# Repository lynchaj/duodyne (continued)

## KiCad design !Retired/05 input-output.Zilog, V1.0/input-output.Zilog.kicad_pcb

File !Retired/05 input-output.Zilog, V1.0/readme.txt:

The input-output.Zilog board provides system timer/counter, dual serial ports, and dual general purpose parallel IO.  It also supports a dedicated controller for extended interrupts.  Designed for IM2, it is intended to be the primary console interface.

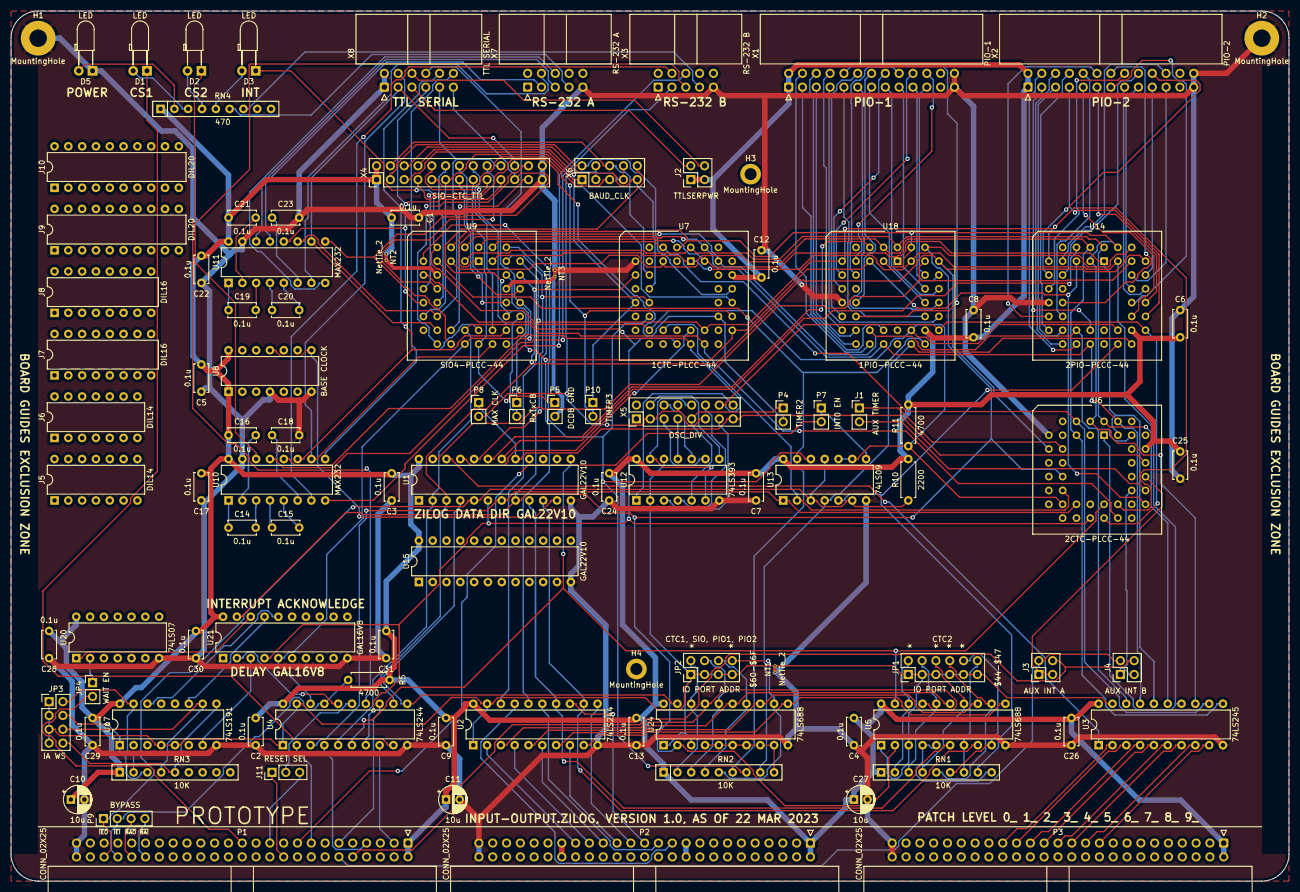
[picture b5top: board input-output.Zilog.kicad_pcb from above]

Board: 2 copper layers, 235.0 x 160.0 mm, 102 parts (0 on the bottom side), 210 nets.

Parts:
C1, C2, C3, C4, C5, C6, C7, C8, C9, C12, C13, C14, C15, C16, C17, C18, C19, C20, C21, C22, C23, C24, C25, C26, C28, C29, C30, C31: 0.1u; C_Disc_D5.0mm_W2.5mm_P5.00mm
C10, C11, C27: 10u; CP_Radial_D5.0mm_P2.50mm
D1, D2, D3, D5: LED; LED_D3.0mm_Horizontal_O3.81mm_Z2.0mm
H1, H2: MountingHole; MountingHole_3.2mm_M3_Pad
H3, H4: MountingHole; MountingHole_2.2mm_M2_DIN965_Pad
J1: AUX TIMER; PinHeader_1x02_P2.54mm_Vertical
J2: TTLSERPWR; PinHeader_2x02_P2.54mm_Vertical
J3: AUX INT A; PinHeader_2x02_P2.54mm_Vertical
J4: AUX INT B; PinHeader_2x02_P2.54mm_Vertical
J5, J6: DIL14; DIP-14_W7.62mm
J7, J8: DIL16; DIP-16_W7.62mm
J9, J10: DIL20; DIP-20_W7.62mm
J11: RESET SEL; PinHeader_1x03_P2.54mm_Vertical
JP1: IO PORT ADDR; PinHeader_2x06_P2.54mm_Vertical
JP2: IO PORT ADDR; PinHeader_2x04_P2.54mm_Vertical
JP3: IA WS; PinHeader_2x04_P2.54mm_Vertical
JP4: WAIT EN; PinHeader_1x02_P2.54mm_Vertical
NT1, NT2, NT3: NetTie_2; NetTie-2_THT_Pad0.3mm
P1, P2, P3: CONN_02X25; IDC-Header_2x25_P2.54mm_Horizontal
P4: TIMER2; PinHeader_1x02_P2.54mm_Vertical
P5: DCDB GND; PinHeader_1x02_P2.54mm_Vertical
P6: RxTxCB; PinHeader_1x02_P2.54mm_Vertical
P7: INT0 EN; PinHeader_1x02_P2.54mm_Vertical
P8: MAX CLK; PinHeader_1x02_P2.54mm_Vertical
P9: BYPASS; PinHeader_1x04_P2.54mm_Vertical
P10: TIMER3; PinHeader_1x02_P2.54mm_Vertical
R5, R11: 4700; R_Axial_DIN0207_L6.3mm_D2.5mm_P7.62mm_Horizontal
R10: 2200; R_Axial_DIN0207_L6.3mm_D2.5mm_P7.62mm_Horizontal
RN1, RN2, RN3: 10K; R_Array_SIP9
RN4: 470; R_Array_SIP9
U1, U15: GAL22V10; DIP-24_W7.62mm
U2, U4: 74LS244; DIP-20_W7.62mm
U3: 74LS245; DIP-20_W7.62mm
U5, U24: 74LS688; DIP-20_W7.62mm
U6: 2CTC-PLCC-44; PLCC-44_THT-Socket
U7: 1CTC-PLCC-44; PLCC-44_THT-Socket
U8: BASE CLOCK; DIP-14_W7.62mm
U9: SIO4-PLCC-44; PLCC-44_THT-Socket
U10, U11: MAX232; DIP-16_W7.62mm
U12: 74LS393; DIP-14_W7.62mm
U13: 74LS09; DIP-14_W7.62mm
U14: 2PIO-PLCC-44; PLCC-44_THT-Socket
U17: 74LS191; DIP-16_W7.62mm
U18: 1PIO-PLCC-44; PLCC-44_THT-Socket
U20: 74LS07; DIP-14_W7.62mm
U21: GAL16V8; DIP-20_W7.62mm
X1: PIO-1; IDC-Header_2x13_P2.54mm_Horizontal
X2: PIO-2; IDC-Header_2x13_P2.54mm_Horizontal
X3: RS-232 B; IDC-Header_2x05_P2.54mm_Horizontal
X4: SIO-CTC_TTL; PinHeader_2x13_P2.54mm_Vertical
X5: OSC_DIV; PinHeader_2x08_P2.54mm_Vertical
X6: BAUD_CLK; PinHeader_2x05_P2.54mm_Vertical
X7: RS-232 A; IDC-Header_2x05_P2.54mm_Horizontal
X8: TTL SERIAL; IDC-Header_2x06_P2.54mm_Horizontal

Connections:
470A: D5.2 (A), RN4.2 (R1)
470B: D1.2 (A), RN4.3 (R2)
470C: D2.2 (A), RN4.4 (R3)
470D: D3.2 (A), RN4.5 (R4)
470E: RN4.6 (R5), X7.7
470F: RN4.7 (R6), X3.7
+12V: P2.19, P2.20
-12V: P2.37, P2.38
/CTC-INT/2CTC_TG1: J3.1, J3.3, U6.33 (CLK/TRG1)
/CTC-INT/2CTC_TG2: J4.1, J4.3, U6.32 (CLK/TRG2)
/CTC-INT/2CTC_TG3: J1.2, U6.31 (CLK/TRG3)
/CTC-INT/2CTC_ZC0: J1.1, U6.10 (ZC/TO0)
/CTC-SIO/1CPA: U12.1 (CP), X5.16
/CTC-SIO/1CTC_TG0: U7.35 (CLK/TRG0), X4.3, X6.2
/CTC-SIO/1CTC_TG1: U7.33 (CLK/TRG1), X4.5, X6.1
/CTC-SIO/1CTC_TG2: P4.2, U7.32 (CLK/TRG2), X4.7
/CTC-SIO/1CTC_TG3: P10.2, U7.31 (CLK/TRG3), X4.9
/CTC-SIO/1CTC_ZC0: U7.10 (ZC/TO0), X4.4, X6.6
/CTC-SIO/1CTC_ZC1: U7.12 (ZC/TO1), X4.6, X6.9
/CTC-SIO/1CTC_ZC2: P10.1, U7.13 (ZC/TO2), X4.8
/CTC-SIO/1CTSA_IN: U11.8 (R2IN), X7.6
/CTC-SIO/1CTSB_IN: U10.8 (R2IN), X3.6
/CTC-SIO/1PHI_X: P8.2 (B), X5.3, X5.8, X5.11, X6.3, X6.4, X6.7, X6.8
/CTC-SIO/1PWRA: J2.2, X8.5
/CTC-SIO/1PWRB: J2.4, X8.6
/CTC-SIO/1Q0A: U12.3 (Q0), X5.13
/CTC-SIO/1Q0B: U12.11 (Q0), X5.7
/CTC-SIO/1Q1A: U12.4 (Q1), X5.12
/CTC-SIO/1Q1B: U12.10 (Q1), X5.6
/CTC-SIO/1Q2A: P4.1, U12.5 (Q2), X5.9
/CTC-SIO/1Q2B: U12.9 (Q2), X5.5
/CTC-SIO/1Q3A: U12.6 (Q3), U12.13 (CP), X5.10
/CTC-SIO/1Q3B: U12.8 (Q3), X5.4
/CTC-SIO/1RTSA_OUT: U11.7 (T2OUT), X7.4
/CTC-SIO/1RTSB_OUT: U10.7 (T2OUT), X3.4
/CTC-SIO/1RXDA: U9.13 (RXDA), U11.12 (R1OUT), X4.19, X8.7
/CTC-SIO/1RXDB: U9.33 (RXDB), U10.12 (R1OUT), X8.8
/CTC-SIO/1TXDA: U9.16 (TXDA), U11.11 (T1IN), X4.20, X8.9
/CTC-SIO/1TXDB: U9.30 (TXDB), U10.11 (T1IN), X8.10
/CTC-SIO/GND-SIO4: NT3.2, P5.2, U9.36 (GND)
/CTC-SIO/VCC-SIO4: NT2.2, U9.10 (+5V)
/CTC-SIO/~1CTSA: U9.20 (~CTSA), U11.9 (R2OUT), X4.21, X8.11
/CTC-SIO/~1CTSB: U9.25 (~CTSB), U10.9 (R2OUT), X8.12
/CTC-SIO/~1DCDA: U9.21 (~DCDA), X4.23
/CTC-SIO/~1DCDB: P5.1, U9.24 (~DCDB), X4.15
/CTC-SIO/~1DTRA: U9.18 (~DTRA), X4.24
/CTC-SIO/~1DTRB: U9.27 (~DTRB), X4.16
/CTC-SIO/~1RIA: U9.12 (~SYNCA), X4.18
/CTC-SIO/~1RIB: U9.34 (~SYNCB), X4.14
/CTC-SIO/~1RTSA: U9.19 (~RTSA), U11.10 (T2IN), X4.22, X8.3
/CTC-SIO/~1RTSB: U9.26 (~RTSB), U10.10 (T2IN), X8.4
/CTC-SIO/~1RXCA: U9.14 (~RXCA), X4.12
/CTC-SIO/~1RXDA_IN: U11.13 (R1IN), X7.3
/CTC-SIO/~1RXDB_IN: U10.13 (R1IN), X3.3
/CTC-SIO/~1RxCB: P6.1, U9.32 (~RXCB), X6.10
/CTC-SIO/~1TXCA: U9.15 (~TXCA), X4.11, X6.5
/CTC-SIO/~1TXCB: P6.2, U9.31 (~TXCB), X4.10
/CTC-SIO/~1TXDA_OUT: U11.14 (T1OUT), X7.5
/CTC-SIO/~1TXDB_OUT: U10.14 (T1OUT), X3.5
/CTC-SIO/~1W-RDYA: U9.11 (~W/~RDYA), X4.17
/CTC-SIO/~1W-RDYB: U9.35 (~W/~RDYB), X4.13
/GAL/DEL_CNT: U17.7 (Q3), U21.3 (I3)
/GAL/bM1: U17.11 (Pl), U21.17 (I03)
/GAL/~bCLK: U17.14 (Cp), U21.16 (IO4)
/GAL/~bWAIT: U20.1, U21.18 (IO2)
/dualPIO/1ARDY: U18.20 (ARDY), X1.4
/dualPIO/1BRDY: U18.23 (BRDY), X1.3
/dualPIO/1PA0: U18.17 (PA0), X1.8
/dualPIO/1PA1: U18.16 (PA1), X1.10
/dualPIO/1PA2: U18.15 (PA2), X1.12
/dualPIO/1PA3: U18.14 (PA3), X1.14
/dualPIO/1PA4: U18.11 (PA4), X1.16
/dualPIO/1PA5: U18.10 (PA5), X1.18
/dualPIO/1PA6: U18.9 (PA6), X1.20
/dualPIO/1PA7: U18.8 (PA7), X1.22
/dualPIO/1PB0: U18.31 (PB0), X1.7
/dualPIO/1PB1: U18.32 (PB1), X1.9
/dualPIO/1PB2: U18.33 (PB2), X1.11
/dualPIO/1PB3: U18.34 (PB3), X1.13
/dualPIO/1PB4: U18.35 (PB4), X1.15
/dualPIO/1PB5: U18.36 (PB5), X1.17
/dualPIO/1PB6: U18.37 (PB6), X1.19
/dualPIO/1PB7: U18.38 (PB7), X1.21
/dualPIO/2ARDY: U14.20 (ARDY), X2.4
/dualPIO/2BRDY: U14.23 (BRDY), X2.3
/dualPIO/2PA0: U14.17 (PA0), X2.8
/dualPIO/2PA1: U14.16 (PA1), X2.10
/dualPIO/2PA2: U14.15 (PA2), X2.12
/dualPIO/2PA3: U14.14 (PA3), X2.14
/dualPIO/2PA4: U14.11 (PA4), X2.16
/dualPIO/2PA5: U14.10 (PA5), X2.18
/dualPIO/2PA6: U14.9 (PA6), X2.20
/dualPIO/2PA7: U14.8 (PA7), X2.22
/dualPIO/2PB0: U14.31 (PB0), X2.7
/dualPIO/2PB1: U14.32 (PB1), X2.9
/dualPIO/2PB2: U14.33 (PB2), X2.11
/dualPIO/2PB3: U14.34 (PB3), X2.13
/dualPIO/2PB4: U14.35 (PB4), X2.15
/dualPIO/2PB5: U14.36 (PB5), X2.17
/dualPIO/2PB6: U14.37 (PB6), X2.19
/dualPIO/2PB7: U14.38 (PB7), X2.21
/dualPIO/~1ASTB: U18.18 (~ASTB), X1.6
/dualPIO/~1BSTB: U18.19 (~BSTB), X1.5
/dualPIO/~2ASTB: U14.18 (~ASTB), X2.6
/dualPIO/~2BSTB: U14.19 (~BSTB), X2.5
A0: P2.35, U2.2 (I0a)
A1: P2.33, U2.4 (I1a)
A2: P2.31, U2.6 (I2a)
A3: P2.29, U2.8 (I3a)
A4: P2.27, U2.11 (I0b)
A5: P2.25, U2.13 (I1b)
A6: P2.23, U2.15 (I2b)
A7: P2.21, U2.17 (I3b)
BASE_CLK: U1.11 (I10), U8.8, U8.11
CLK: P1.15, U4.2 (I0a)
CLK_ZILOG: P8.1 (A), U1.17 (O6), U6.35 (CLK/TRG0), X5.15
D0: P3.33, U3.2 (A0)
D1: P3.31, U3.3 (A1)
D2: P3.29, U3.4 (A2)
D3: P3.27, U3.5 (A3)
D4: P3.25, U3.6 (A4)
D5: P3.23, U3.7 (A5)
D6: P3.21, U3.8 (A6)
D7: P3.19, U3.9 (A7)
DATA_DIR: U1.22 (O1), U3.1 (A->B)
GND: C1.2, C2.2, C3.2, C4.2, C5.2, C6.2, C7.2, C8.2, C9.2, C10.2, C11.2, C12.2, C13.2, C17.2, C18.2, C22.2, C23.2, C24.2, C25.2, C26.2, C27.2, C28.2, C29.2, C30.2, C31.2, D5.1 (K), H1.1, H2.1, NT1.1, NT3.1, P1.49, P1.50, P2.49, P2.50, P3.49, P3.50, U1.12 (GND), U2.10 (GND), U3.10 (GND), U4.10 (GND), U5.10 (GND), U6.7 (GND), U7.7 (GND), U8.4, U8.7, U10.15 (GND), U11.15 (GND), U12.7 (GND), U13.7 (GND), U14.13 (GND), U15.12 (GND), U17.8 (GND), U18.13 (GND), U20.7 (GND), U21.10 (GND), U24.10 (GND), X1.25, X1.26, X2.25, X2.26, X3.9, X4.25, X4.26, X7.9, X8.1, X8.2
IEO_CTC1: RN2.7 (R6), U7.16 (IEO), U9.7 (IEI), U13.12
IEO_CTC2: U6.16 (IEO), U7.21 (IEI), U13.2
IEO_PIO1: RN2.8 (R7), U13.4, U14.28 (IEI), U18.26 (IEO)
IEO_PIO2: RN1.8 (R7), U13.5, U14.26 (IEO)
IEO_SIO1: RN2.6 (R5), U9.8 (IEO), U13.13, U18.28 (IEI)
unnamed: C14.1, U10.1 (C1+)
unnamed: C14.2, U10.3 (C1-)
unnamed: C15.1, U10.4 (C2+)
unnamed: C15.2, U10.5 (C2-)
unnamed: C16.2, U10.2 (VS+)
unnamed: C18.1, U10.6 (VS-)
unnamed: C19.1, U11.1 (C1+)
unnamed: C19.2, U11.3 (C1-)
unnamed: C20.1, U11.4 (C2+)
unnamed: C20.2, U11.5 (C2-)
unnamed: C21.2, U11.2 (VS+)
unnamed: C23.1, U11.6 (VS-)
unnamed: D1.1 (K), U4.9 (O0b)
unnamed: D2.1 (K), U4.14 (O2a)
unnamed: J11.2, U4.15 (I2b)
unnamed: JP1.2, RN1.2 (R1), U5.18 (R7)
unnamed: JP1.4, RN1.3 (R2), U5.16 (R6)
unnamed: JP1.6, RN1.4 (R3), U5.14 (R5)
unnamed: JP1.8, RN1.5 (R4), U5.12 (R4)
unnamed: JP1.10, RN1.6 (R5), U5.9 (R3)
unnamed: JP1.12, RN1.7 (R6), U5.7 (R2)
unnamed: JP2.2, RN2.2 (R1), U24.18 (R7)
unnamed: JP2.4, RN2.3 (R2), U24.16 (R6)
unnamed: JP2.6, RN2.4 (R3), U24.14 (R5)
unnamed: JP2.8, RN2.5 (R4), U24.12 (R4)
unnamed: JP3.2, RN3.2 (R1), U17.15 (P0)
unnamed: JP3.4, RN3.3 (R2), U17.1
unnamed: JP3.6, RN3.4 (R3), U17.10 (P2)
unnamed: JP3.8, RN3.5 (R4), U17.9 (P3)
unnamed: JP4.1 (A), U20.2
unnamed: P7.1 (A), U13.8
unnamed: RN1.9 (R8), U5.4 (P1), U5.5 (R1)
unnamed: RN2.9 (R8), U24.4 (P1), U24.5 (R1), U24.6 (P2), U24.7 (R2), U24.8 (P3), U24.9 (R3)
VCC: C1.1, C2.1, C3.1, C4.1, C5.1, C6.1, C7.1, C8.1, C9.1, C10.1, C11.1, C12.1, C13.1, C16.1, C17.1, C21.1, C22.1, C24.1, C25.1, C26.1, C27.1, C28.1, C29.1, C30.1, C31.1, J2.1, J2.3, NT2.1, P1.1, P1.2, P2.1, P2.2, P3.1, P3.2, R5.2, R10.2, R11.2, RN1.1 (common), RN2.1 (common), RN3.1 (common), RN4.1 (common), U1.24 (VCC), U2.20 (VCC), U3.20 (VCC), U4.20 (VCC), U5.20 (VCC), U6.37 (+5V), U7.37 (+5V), U8.1, U8.14, U10.16 (VCC), U11.16 (VCC), U12.14 (VCC), U13.14 (VCC), U14.30 (VCC), U15.24 (VCC), U17.16 (VCC), U18.30 (VCC), U20.14 (VCC), U21.20 (VCC), U24.20 (VCC), X1.1, X1.2, X2.1, X2.2, X4.1, X4.2
ZERO: JP1.1, JP1.3, JP1.5, JP1.7, JP1.9, JP1.11, JP2.1, JP2.3, JP2.5, JP2.7, JP3.1, JP3.3, JP3.5, JP3.7, NT1.2, U2.1 (OEa), U2.19 (OEb), U3.19 (CE), U4.1 (OEa), U4.19 (OEb), U5.1 (G), U5.3 (R0), U12.2 (MR), U12.12 (MR), U17.4 (Ce), U17.5 (D/U), U24.1 (G), U24.3 (R0)
bA0: U2.18 (O0a), U6.27 (CS0), U7.27 (CS0), U9.39 (B/~A), U14.7 (B/~A), U18.7 (B/~A)
bA1: U2.16 (O1a), U6.29 (CS1), U7.29 (CS1), U9.38 (C/~D), U14.5 (C/~D), U18.5 (C/~D)
bA2: U1.9 (I8), U2.14 (O2a), U5.6 (P2)
bA3: U1.10 (I9), U2.12 (O3a), U5.8 (P3)
bA4: U2.9 (O0b), U5.11 (P4), U24.11 (P4)
bA5: U2.7 (O1b), U5.13 (P5), U24.13 (P5)
bA6: U2.5 (O2b), U5.15 (P6), U24.15 (P6)
bA7: U2.3 (O3b), U5.17 (P7), U24.17 (P7)
bCLK: U4.18 (O0a), U6.24 (CLK), U7.24 (CLK), U9.22 (CLK), U14.29 (CLK), U18.29 (CLK), U21.5 (I5), X5.14
bD0: U3.18 (B0), U6.41 (D0), U7.41 (D0), U9.1 (D0), U14.21 (D0), U18.21 (D0)
bD1: U3.17 (B1), U6.42 (D1), U7.42 (D1), U9.2 (D1), U14.22 (D1), U18.22 (D1)
bD2: U3.16 (B2), U6.43 (D2), U7.43 (D2), U9.44 (D2), U14.1 (D2), U18.1 (D2)
bD3: U3.15 (B3), U6.44 (D3), U7.44 (D3), U9.3 (D3), U14.44 (D3), U18.44 (D3)
bD4: U3.14 (B4), U6.1 (D4), U7.1 (D4), U9.43 (D4), U14.43 (D4), U18.43 (D4)
bD5: U3.13 (B5), U6.2 (D5), U7.2 (D5), U9.4 (D5), U14.3 (D6), U14.42 (D5), U18.3 (D6), U18.42 (D5)
bD6: U3.12 (B6), U6.4 (D6), U7.4 (D6), U9.42 (D6)
bD7: U3.11 (B7), U6.5 (D7), U7.5 (D7), U9.5 (D7), U14.2 (D7), U18.2 (D7)
~BAI: P1.40, P9.4
~BAO: P1.42, P9.3
~CS1: U1.4 (I3), U4.11 (I0b), U24.19 (P=R)
~CS2: U1.13 (I11), U4.6 (I2a), U5.19 (P=R), U6.25 (~CE)
~CS_CTC1: U1.21 (O2), U7.25 (~CE)
~CS_PIO1: U1.19 (O4), U18.4 (~CE)
~CS_PIO2: U1.18 (O5), U14.4 (~CE)
~CS_SIO1: U1.20 (O3), U9.40 (~CE)
~IEI: P1.44, P9.2, R5.1, U4.17 (I3b)
~IEO: P1.46, P9.1, R10.1, U1.5 (I4), U13.3, U13.6, U13.11
~INT0: P1.17, P7.2 (B)
~INT1: J3.2, J4.2, P1.12
~INT2: J3.4, J4.4, P1.10
~IORQ: P1.7, U4.4 (I1a)
~M1: P1.11, U4.13 (I1b)
~PM1: U1.23 (O0), U14.41 (~M1), U18.41 (~M1)
~RD: P1.3, U4.8 (I3a)
~RES_IN: J11.1, P1.20
~RES_OUT: J11.3, P1.21
~WAIT: JP4.2 (B), P1.25
~bIEI: U1.7 (I6), U4.3 (O3b), U6.21 (IEI), U13.1
~bINT: D3.1 (K), R11.1, U6.19 (~INT), U7.19 (~INT), U9.6 (~INT), U13.9, U13.10, U14.27 (~INT), U18.27 (~INT)
~bIORQ_RAW: U4.16 (O1a), U21.2 (I2)
~bIORQ: U1.8 (I7), U5.2 (P0), U6.14 (~IORQ), U7.14 (~IORQ), U9.41 (~IORQ), U14.40 (~IORQ), U18.40 (~IORQ), U21.19 (IO1), U24.2 (P0)
~bM1: U1.6 (I5), U4.7 (O1b), U6.22 (~M1), U7.22 (~M1), U9.9 (~M1), U21.4 (I4)
~bRD: U1.3 (I2), U4.12 (O3a), U6.9 (~RD), U7.9 (~RD), U9.37 (~RD), U14.39 (~RD), U18.39 (~RD)
~bRESET: U1.2 (I1), U4.5 (O2b), U6.26 (~RESET), U7.26 (~RESET), U9.23 (~RESET)

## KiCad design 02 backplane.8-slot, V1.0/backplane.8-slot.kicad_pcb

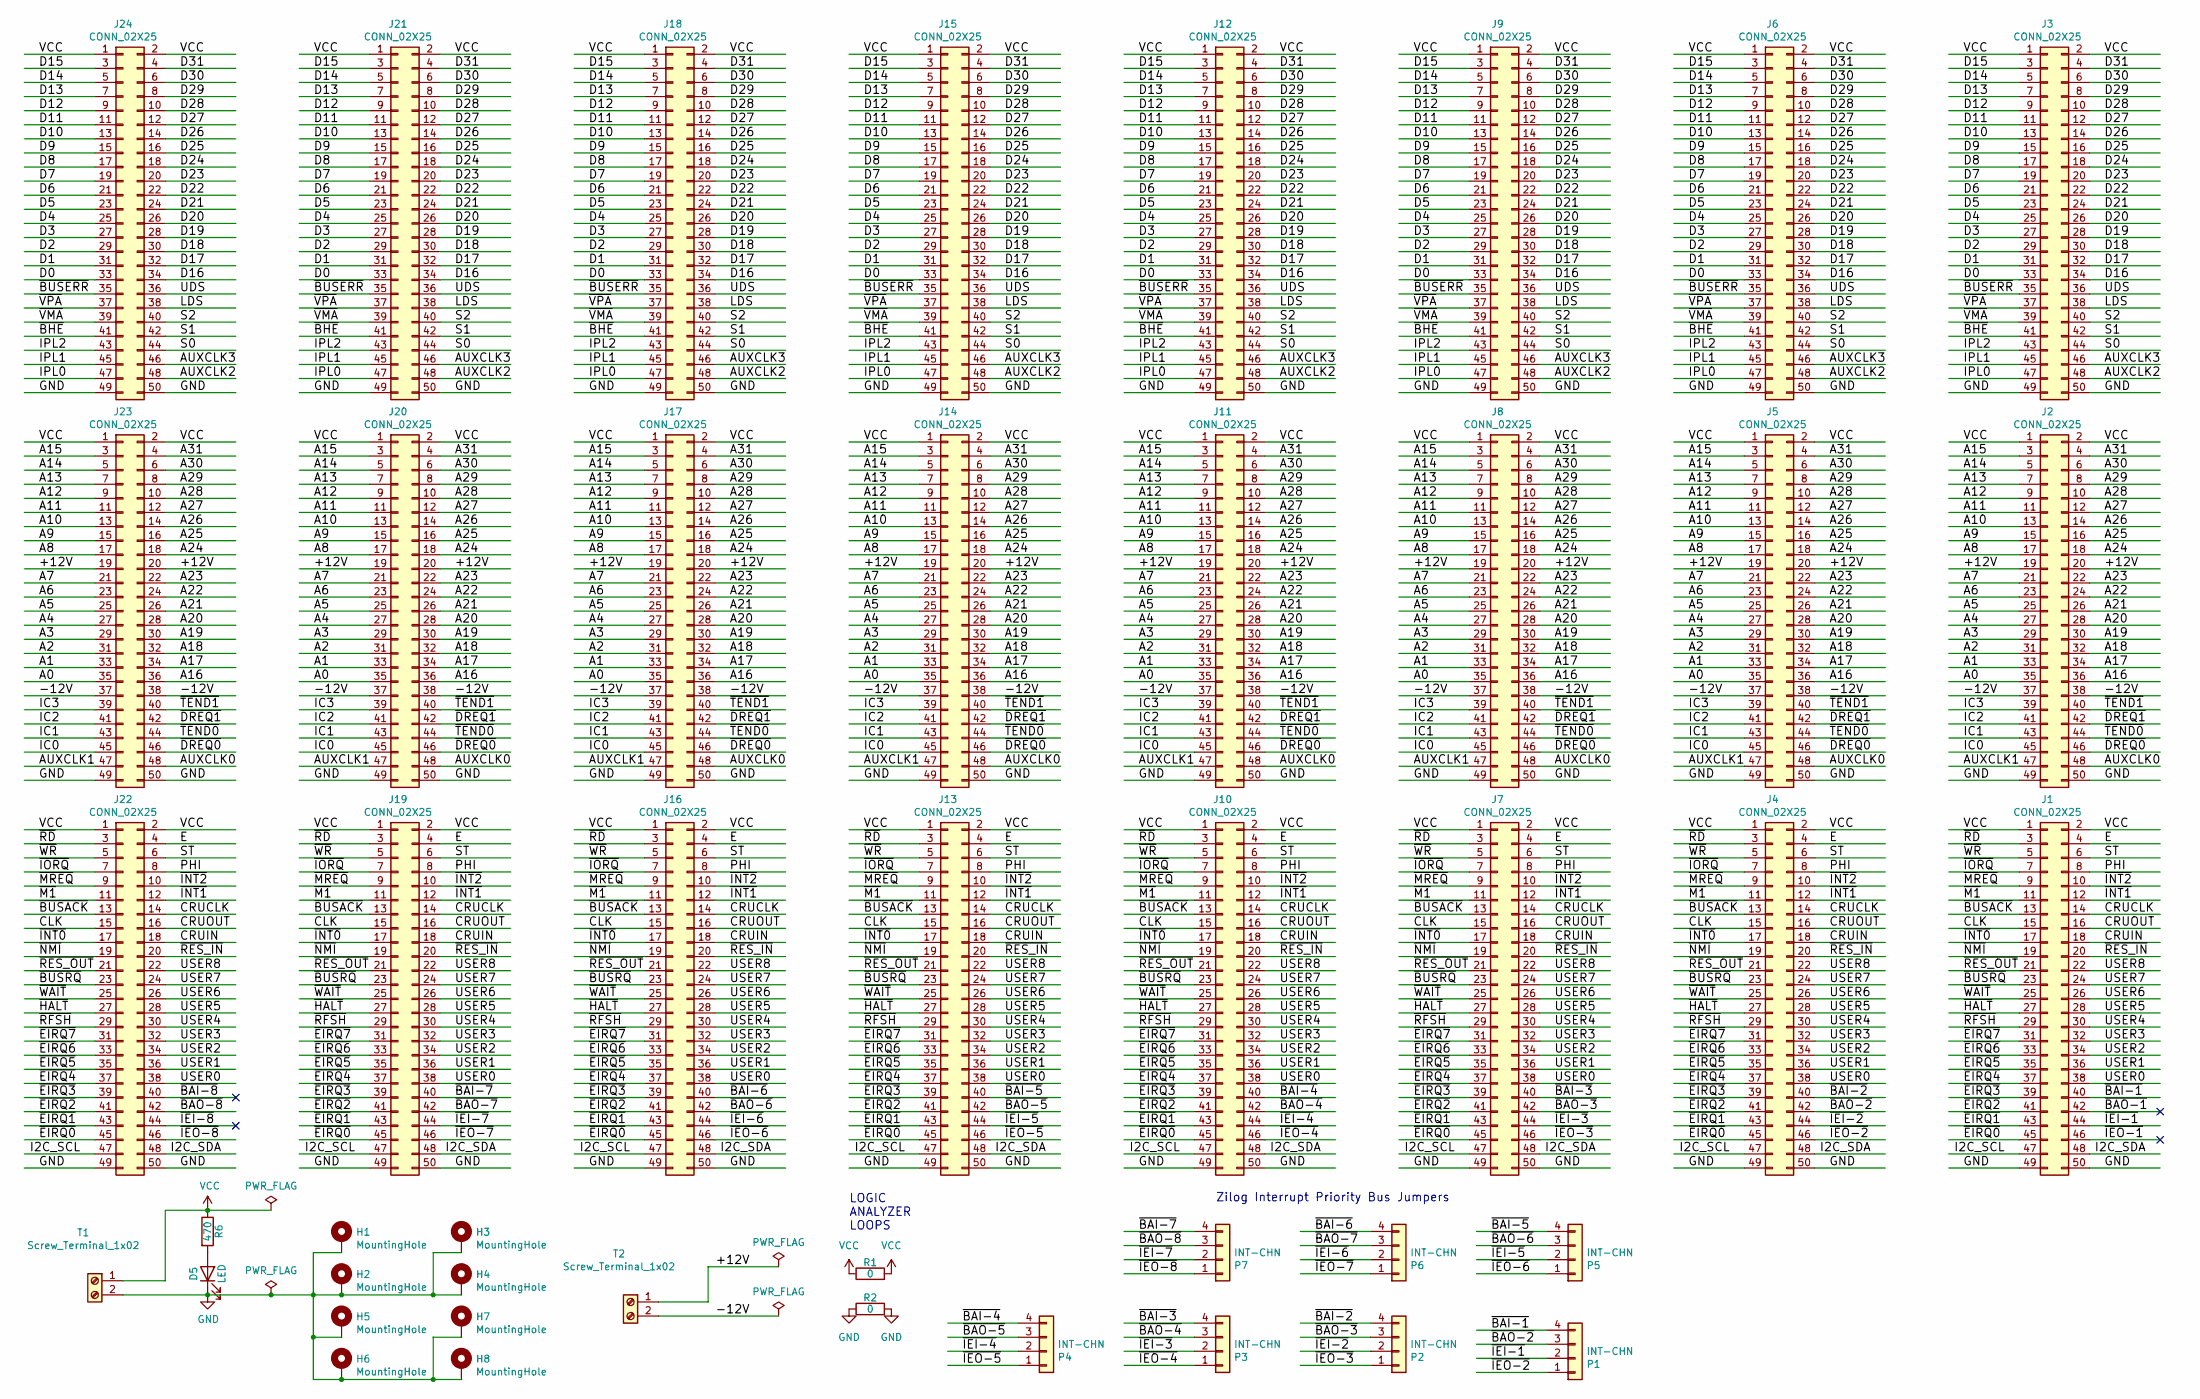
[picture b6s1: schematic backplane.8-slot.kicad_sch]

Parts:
D5: LED; LED_D3.0mm
H1, H2, H3, H4, H5, H6, H7, H8: MountingHole; MountingHole_3.2mm_M3_Pad
J1, J2, J3, J4, J5, J6, J7, J8, J9, J10, J11, J12, J13, J14, J15, J16, J17, J18, J19, J20, J21, J22, J23, J24: CONN_02X25; PinSocket_2x25_P2.54mm_Vertical
P1, P2, P3, P4, P5, P6, P7: INT-CHN; PinHeader_1x04_P2.54mm_Vertical
R1, R2: 0; R_Axial_DIN0207_L6.3mm_D2.5mm_P7.62mm_Horizontal
R6: 470; R_Axial_DIN0207_L6.3mm_D2.5mm_P7.62mm_Horizontal
T1, T2: Screw_Terminal_1x02; TerminalBlock_Phoenix_MKDS-1,5-2-5.08_1x02_P5.08mm_Horizont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

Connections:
/+12V: J2.19, J2.20, J5.19, J5.20, J8.19, J8.20, J11.19, J11.20, J14.19, J14.20, J17.19, J17.20, J20.19, J20.20, J23.19, J23.20, T2.1
/-12V: J2.37, J2.38, J5.37, J5.38, J8.37, J8.38, J11.37, J11.38, J14.37, J14.38, J17.37, J17.38, J20.37, J20.38, J23.37, J23.38, T2.2
/A0: J2.35, J5.35, J8.35, J11.35, J14.35, J17.35, J20.35, J23.35
/A1: J2.33, J5.33, J8.33, J11.33, J14.33, J17.33, J20.33, J23.33
/A2: J2.31, J5.31, J8.31, J11.31, J14.31, J17.31, J20.31, J23.31
/A3: J2.29, J5.29, J8.29, J11.29, J14.29, J17.29, J20.29, J23.29
/A4: J2.27, J5.27, J8.27, J11.27, J14.27, J17.27, J20.27, J23.27
/A5: J2.25, J5.25, J8.25, J11.25, J14.25, J17.25, J20.25, J23.25
/A6: J2.23, J5.23, J8.23, J11.23, J14.23, J17.23, J20.23, J23.23
/A7: J2.21, J5.21, J8.21, J11.21, J14.21, J17.21, J20.21, J23.21
/A8: J2.17, J5.17, J8.17, J11.17, J14.17, J17.17, J20.17, J23.17
/A9: J2.15, J5.15, J8.15, J11.15, J14.15, J17.15, J20.15, J23.15
/A10: J2.13, J5.13, J8.13, J11.13, J14.13, J17.13, J20.13, J23.13
/A11: J2.11, J5.11, J8.11, J11.11, J14.11, J17.11, J20.11, J23.11
/A12: J2.9, J5.9, J8.9, J11.9, J14.9, J17.9, J20.9, J23.9
/A13: J2.7, J5.7, J8.7, J11.7, J14.7, J17.7, J20.7, J23.7
/A14: J2.5, J5.5, J8.5, J11.5, J14.5, J17.5, J20.5, J23.5
/A15: J2.3, J5.3, J8.3, J11.3, J14.3, J17.3, J20.3, J23.3
/A16: J2.36, J5.36, J8.36, J11.36, J14.36, J17.36, J20.36, J23.36
/A17: J2.34, J5.34, J8.34, J11.34, J14.34, J17.34, J20.34, J23.34
/A18: J2.32, J5.32, J8.32, J11.32, J14.32, J17.32, J20.32, J23.32
/A19: J2.30, J5.30, J8.30, J11.30, J14.30, J17.30, J20.30, J23.30
/A20: J2.28, J5.28, J8.28, J11.28, J14.28, J17.28, J20.28, J23.28
/A21: J2.26, J5.26, J8.26, J11.26, J14.26, J17.26, J20.26, J23.26
/A22: J2.24, J5.24, J8.24, J11.24, J14.24, J17.24, J20.24, J23.24
/A23: J2.22, J5.22, J8.22, J11.22, J14.22, J17.22, J20.22, J23.22
/A24: J2.18, J5.18, J8.18, J11.18, J14.18, J17.18, J20.18, J23.18
/A25: J2.16, J5.16, J8.16, J11.16, J14.16, J17.16, J20.16, J23.16
/A26: J2.14, J5.14, J8.14, J11.14, J14.14, J17.14, J20.14, J23.14
/A27: J2.12, J5.12, J8.12, J11.12, J14.12, J17.12, J20.12, J23.12
/A28: J2.10, J5.10, J8.10, J11.10, J14.10, J17.10, J20.10, J23.10
/A29: J2.8, J5.8, J8.8, J11.8, J14.8, J17.8, J20.8, J23.8
/A30: J2.6, J5.6, J8.6, J11.6, J14.6, J17.6, J20.6, J23.6
/A31: J2.4, J5.4, J8.4, J11.4, J14.4, J17.4, J20.4, J23.4
/AUXCLK0: J2.48, J5.48, J8.48, J11.48, J14.48, J17.48, J20.48, J23.48
/AUXCLK1: J2.47, J5.47, J8.47, J11.47, J14.47, J17.47, J20.47, J23.47
/AUXCLK2: J3.48, J6.48, J9.48, J12.48, J15.48, J18.48, J21.48, J24.48
/AUXCLK3: J3.46, J6.46, J9.46, J12.46, J15.46, J18.46, J21.46, J24.46
/CLK: J1.15, J4.15, J7.15, J10.15, J13.15, J16.15, J19.15, J22.15
/CRUCLK: J1.14, J4.14, J7.14, J10.14, J13.14, J16.14, J19.14, J22.14
/CRUIN: J1.18, J4.18, J7.18, J10.18, J13.18, J16.18, J19.18, J22.18
/CRUOUT: J1.16, J4.16, J7.16, J10.16, J13.16, J16.16, J19.16, J22.16
/D0: J3.33, J6.33, J9.33, J12.33, J15.33, J18.33, J21.33, J24.33
/D1: J3.31, J6.31, J9.31, J12.31, J15.31, J18.31, J21.31, J24.31
/D2: J3.29, J6.29, J9.29, J12.29, J15.29, J18.29, J21.29, J24.29
/D3: J3.27, J6.27, J9.27, J12.27, J15.27, J18.27, J21.27, J24.27
/D4: J3.25, J6.25, J9.25, J12.25, J15.25, J18.25, J21.25, J24.25
/D5: J3.23, J6.23, J9.23, J12.23, J15.23, J18.23, J21.23, J24.23
/D6: J3.21, J6.21, J9.21, J12.21, J15.21, J18.21, J21.21, J24.21
/D7: J3.19, J6.19, J9.19, J12.19, J15.19, J18.19, J21.19, J24.19
/D8: J3.17, J6.17, J9.17, J12.17, J15.17, J18.17, J21.17, J24.17
/D9: J3.15, J6.15, J9.15, J12.15, J15.15, J18.15, J21.15, J24.15
/D10: J3.13, J6.13, J9.13, J12.13, J15.13, J18.13, J21.13, J24.13
/D11: J3.11, J6.11, J9.11, J12.11, J15.11, J18.11, J21.11, J24.11
/D12: J3.9, J6.9, J9.9, J12.9, J15.9, J18.9, J21.9, J24.9
/D13: J3.7, J6.7, J9.7, J12.7, J15.7, J18.7, J21.7, J24.7
/D14: J3.5, J6.5, J9.5, J12.5, J15.5, J18.5, J21.5, J24.5
/D15: J3.3, J6.3, J9.3, J12.3, J15.3, J18.3, J21.3, J24.3
/D16: J3.34, J6.34, J9.34, J12.34, J15.34, J18.34, J21.34, J24.34
/D17: J3.32, J6.32, J9.32, J12.32, J15.32, J18.32, J21.32, J24.32
/D18: J3.30, J6.30, J9.30, J12.30, J15.30, J18.30, J21.30, J24.30
/D19: J3.28, J6.28, J9.28, J12.28, J15.28, J18.28, J21.28, J24.28
/D20: J3.26, J6.26, J9.26, J12.26, J15.26, J18.26, J21.26, J24.26
/D21: J3.24, J6.24, J9.24, J12.24, J15.24, J18.24, J21.24, J24.24
/D22: J3.22, J6.22, J9.22, J12.22, J15.22, J18.22, J21.22, J24.22
/D23: J3.20, J6.20, J9.20, J12.20, J15.20, J18.20, J21.20, J24.20
/D24: J3.18, J6.18, J9.18, J12.18, J15.18, J18.18, J21.18, J24.18
/D25: J3.16, J6.16, J9.16, J12.16, J15.16, J18.16, J21.16, J24.16
/D26: J3.14, J6.14, J9.14, J12.14, J15.14, J18.14, J21.14, J24.14
/D27: J3.12, J6.12, J9.12, J12.12, J15.12, J18.12, J21.12, J24.12
/D28: J3.10, J6.10, J9.10, J12.10, J15.10, J18.10, J21.10, J24.10
/D29: J3.8, J6.8, J9.8, J12.8, J15.8, J18.8, J21.8, J24.8
/D30: J3.6, J6.6, J9.6, J12.6, J15.6, J18.6, J21.6, J24.6
/D31: J3.4, J6.4, J9.4, J12.4, J15.4, J18.4, J21.4, J24.4
/E: J1.4, J4.4, J7.4, J10.4, J13.4, J16.4, J19.4, J22.4
/I2C_SCL: J1.47, J4.47, J7.47, J10.47, J13.47, J16.47, J19.47, J22.47
/I2C_SDA: J1.48, J4.48, J7.48, J10.48, J13.48, J16.48, J19.48, J22.48
/IC0: J2.45, J5.45, J8.45, J11.45, J14.45, J17.45, J20.45, J23.45
/IC1: J2.43, J5.43, J8.43, J11.43, J14.43, J17.43, J20.43, J23.43
/IC2: J2.41, J5.41, J8.41, J11.41, J14.41, J17.41, J20.41, J23.41
/IC3: J2.39, J5.39, J8.39, J11.39, J14.39, J17.39, J20.39, J23.39
/IPL0: J3.47, J6.47, J9.47, J12.47, J15.47, J18.47, J21.47, J24.47
/IPL1: J3.45, J6.45, J9.45, J12.45, J15.45, J18.45, J21.45, J24.45
/IPL2: J3.43, J6.43, J9.43, J12.43, J15.43, J18.43, J21.43, J24.43
/LDS: J3.38, J6.38, J9.38, J12.38, J15.38, J18.38, J21.38, J24.38
/PHI: J1.8, J4.8, J7.8, J10.8, J13.8, J16.8, J19.8, J22.8
/S0: J3.44, J6.44, J9.44, J12.44, J15.44, J18.44, J21.44, J24.44
/S1: J3.42, J6.42, J9.42, J12.42, J15.42, J18.42, J21.42, J24.42
/S2: J3.40, J6.40, J9.40, J12.40, J15.40, J18.40, J21.40, J24.40
/ST: J1.6, J4.6, J7.6, J10.6, J13.6, J16.6, J19.6, J22.6
/UDS: J3.36, J6.36, J9.36, J12.36, J15.36, J18.36, J21.36, J24.36
/USER0: J1.38, J4.38, J7.38, J10.38, J13.38, J16.38, J19.38, J22.38
/USER1: J1.36, J4.36, J7.36, J10.36, J13.36, J16.36, J19.36, J22.36
/USER2: J1.34, J4.34, J7.34, J10.34, J13.34, J16.34, J19.34, J22.34
/USER3: J1.32, J4.32, J7.32, J10.32, J13.32, J16.32, J19.32, J22.32
/USER4: J1.30, J4.30, J7.30, J10.30, J13.30, J16.30, J19.30, J22.30
/USER5: J1.28, J4.28, J7.28, J10.28, J13.28, J16.28, J19.28, J22.28
/USER6: J1.26, J4.26, J7.26, J10.26, J13.26, J16.26, J19.26, J22.26
/USER7: J1.24, J4.24, J7.24, J10.24, J13.24, J16.24, J19.24, J22.24
/USER8: J1.22, J4.22, J7.22, J10.22, J13.22, J16.22, J19.22, J22.22
/~BAI-1: J1.40, P1.4
/~BAI-2: J4.40, P2.4
/~BAI-3: J7.40, P3.4
/~BAI-4: J10.40, P4.4
/~BAI-5: J13.40, P5.4
/~BAI-6: J16.40, P6.4
/~BAI-7: J19.40, P7.4
/~BAI-8: J22.40
/~BAO-1: J1.42
/~BAO-2: J4.42, P1.3
/~BAO-3: J7.42, P2.3
/~BAO-4: J10.42, P3.3
/~BAO-5: J13.42, P4.3
/~BAO-6: J16.42, P5.3
/~BAO-7: J19.42, P6.3
/~BAO-8: J22.42, P7.3
/~BHE: J3.41, J6.41, J9.41, J12.41, J15.41, J18.41, J21.41, J24.41
/~BUSACK: J1.13, J4.13, J7.13, J10.13, J13.13, J16.13, J19.13, J22.13
/~BUSERR: J3.35, J6.35, J9.35, J12.35, J15.35, J18.35, J21.35, J24.35
/~BUSRQ: J1.23, J4.23, J7.23, J10.23, J13.23, J16.23, J19.23, J22.23
/~DREQ0: J2.46, J5.46, J8.46, J11.46, J14.46, J17.46, J20.46, J23.46
/~DREQ1: J2.42, J5.42, J8.42, J11.42, J14.42, J17.42, J20.42, J23.42
/~EIRQ0: J1.45, J4.45, J7.45, J10.45, J13.45, J16.45, J19.45, J22.45
/~EIRQ1: J1.43, J4.43, J7.43, J10.43, J13.43, J16.43, J19.43, J22.43
/~EIRQ2: J1.41, J4.41, J7.41, J10.41, J13.41, J16.41, J19.41, J22.41
/~EIRQ3: J1.39, J4.39, J7.39, J10.39, J13.39, J16.39, J19.39, J22.39
/~EIRQ4: J1.37, J4.37, J7.37, J10.37, J13.37, J16.37, J19.37, J22.37
/~EIRQ5: J1.35, J4.35, J7.35, J10.35, J13.35, J16.35, J19.35, J22.35
/~EIRQ6: J1.33, J4.33, J7.33, J10.33, J13.33, J16.33, J19.33, J22.33
/~EIRQ7: J1.31, J4.31, J7.31, J10.31, J13.31, J16.31, J19.31, J22.31
/~HALT: J1.27, J4.27, J7.27, J10.27, J13.27, J16.27, J19.27, J22.27
/~IEI-1: J1.44, P1.2
/~IEI-2: J4.44, P2.2
/~IEI-3: J7.44, P3.2
/~IEI-4: J10.44, P4.2
/~IEI-5: J13.44, P5.2
/~IEI-6: J16.44, P6.2
/~IEI-7: J19.44, P7.2
/~IEI-8: J22.44
/~IEO-1: J1.46
/~IEO-2: J4.46, P1.1
/~IEO-3: J7.46, P2.1
/~IEO-4: J10.46, P3.1
/~IEO-5: J13.46, P4.1
/~IEO-6: J16.46, P5.1
/~IEO-7: J19.46, P6.1
/~IEO-8: J22.46, P7.1
/~INT0: J1.17, J4.17, J7.17, J10.17, J13.17, J16.17, J19.17, J22.17
/~INT1: J1.12, J4.12, J7.12, J10.12, J13.12, J16.12, J19.12, J22.12
/~INT2: J1.10, J4.10, J7.10, J10.10, J13.10, J16.10, J19.10, J22.10
/~IORQ: J1.7, J4.7, J7.7, J10.7, J13.7, J16.7, J19.7, J22.7
/~M1: J1.11, J4.11, J7.11, J10.11, J13.11, J16.11, J19.11, J22.11
/~MREQ: J1.9, J4.9, J7.9, J10.9, J13.9, J16.9, J19.9, J22.9
/~NMI: J1.19, J4.19, J7.19, J10.19, J13.19, J16.19, J19.19, J22.19
/~RD: J1.3, J4.3, J7.3, J10.3, J13.3, J16.3, J19.3, J22.3
/~RES_IN: J1.20, J4.20, J7.20, J10.20, J13.20, J16.20, J19.20, J22.20
/~RES_OUT: J1.21, J4.21, J7.21, J10.21, J13.21, J16.21, J19.21, J22.21
/~RFSH: J1.29, J4.29, J7.29, J10.29, J13.29, J16.29, J19.29, J22.29
/~TEND0: J2.44, J5.44, J8.44, J11.44, J14.44, J17.44, J20.44, J23.44
/~TEND1: J2.40, J5.40, J8.40, J11.40, J14.40, J17.40, J20.40, J23.40
/~VMA: J3.39, J6.39, J9.39, J12.39, J15.39, J18.39, J21.39, J24.39
/~VPA: J3.37, J6.37, J9.37, J12.37, J15.37, J18.37, J21.37, J24.37
/~WAIT: J1.25, J4.25, J7.25, J10.25, J13.25, J16.25, J19.25, J22.25
/~WR: J1.5, J4.5, J7.5, J10.5, J13.5, J16.5, J19.5, J22.5
GND: D5.1 (K), H1.1, H2.1, H3.1, H4.1, H5.1, H6.1, H7.1, H8.1, J1.49, J1.50, J2.49, J2.50, J3.49, J3.50, J4.49, J4.50, J5.49, J5.50, J6.49, J6.50, J7.49, J7.50, J8.49, J8.50, J9.49, J9.50, J10.49, J10.50, J11.49, J11.50, J12.49, J12.50, J13.49, J13.50, J14.49, J14.50, J15.49, J15.50, J16.49, J16.50, J17.49, J17.50, J18.49, J18.50, J19.49, J19.50, J20.49, J20.50, J21.49, J21.50, J22.49, J22.50, J23.49, J23.50, J24.49, J24.50, R2.1, R2.2, T1.2
unnamed: D5.2 (A), R6.2
VCC: J1.1, J1.2, J2.1, J2.2, J3.1, J3.2, J4.1, J4.2, J5.1, J5.2, J6.1, J6.2, J7.1, J7.2, J8.1, J8.2, J9.1, J9.2, J10.1, J10.2, J11.1, J11.2, J12.1, J12.2, J13.1, J13.2, J14.1, J14.2, J15.1, J15.2, J16.1, J16.2, J17.1, J17.2, J18.1, J18.2, J19.1, J19.2, J20.1, J20.2, J21.1, J21.2, J22.1, J22.2, J23.1, J23.2, J24.1, J24.2, R1.1, R1.2, R6.1, T1.1

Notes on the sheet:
Zilog Interrupt Priority Bus Jumpers
LOGIC ANALYZER LOOPS

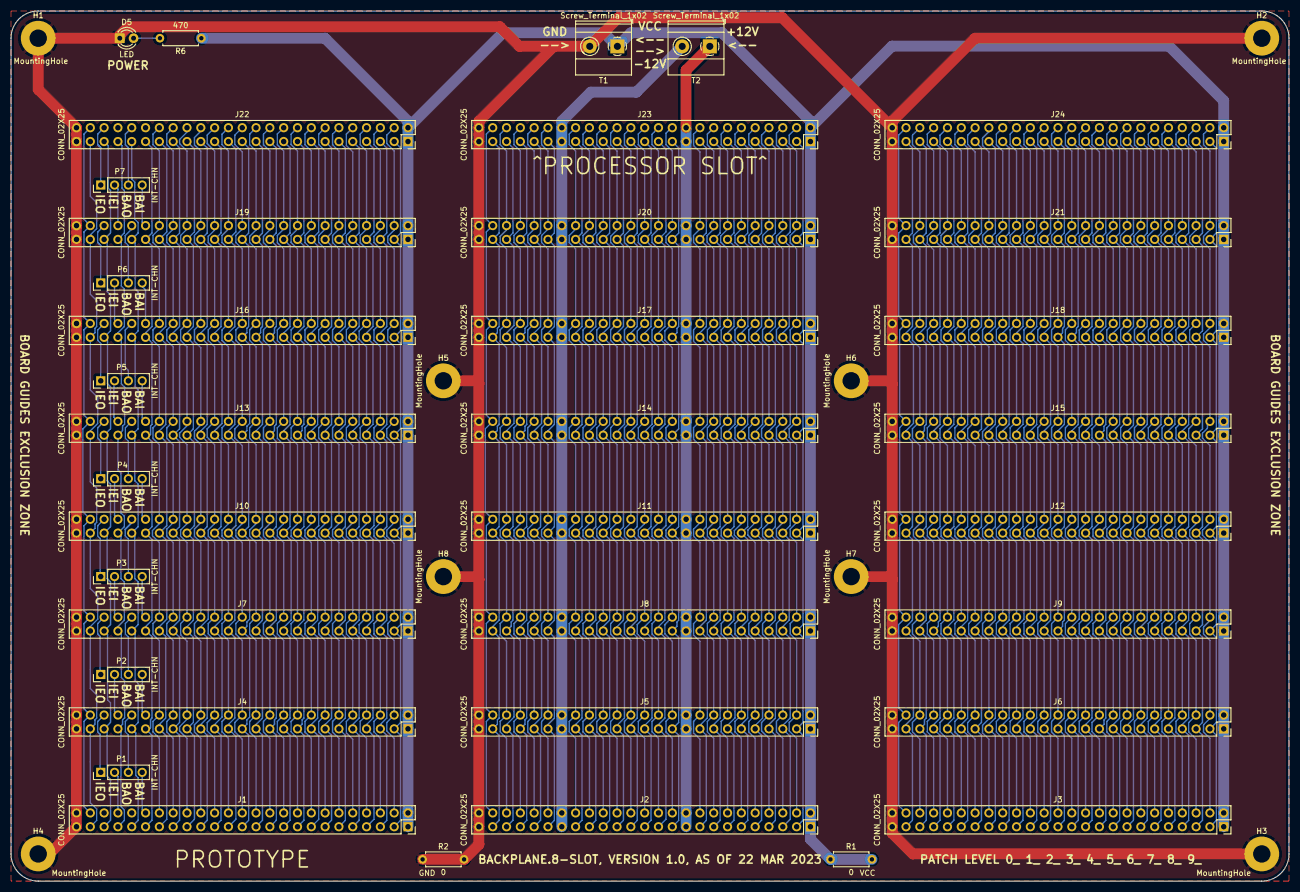
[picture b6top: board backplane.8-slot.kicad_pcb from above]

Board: 2 copper layers, 235.0 x 160.0 mm, 45 parts (0 on the bottom side), 163 nets.
